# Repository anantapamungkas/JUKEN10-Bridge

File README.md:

# JUKEN10 Bridge

Repositori ini berisi berkas desain elektronik JUKEN10 Bridge yang dibuat menggunakan KiCad. Desain skematik dibagi ke beberapa bagian agar rangkaian lebih mudah ditinjau dan dikembangkan.

## Isi repositori

- `JUKEN10 Bridge.kicad_pro` — berkas proyek KiCad.
- `JUKEN10 Bridge.kicad_sch` — skematik utama proyek.
- `JUKEN10 Bridge.kicad_pcb` — berkas tata letak PCB.
- `Section A - Power.kicad_sch` — bagian rangkaian catu daya.
- `Section B - MCU_sch.kicad_sch` — bagian rangkaian mikrokontroler.
- `Section C - Throtle.kicad_sch` — bagian rangkaian throttle.
- `Section D - Input.kicad_sch` — bagian rangkaian input.
- `Section E - Analog Input.kicad_sch` — bagian rangkaian input analog.
- `project_architecture.kicad_sch` — skematik arsitektur proyek.

## Membuka proyek

1. Pasang KiCad 10 atau versi yang lebih baru.
2. Buka `JUKEN10 Bridge.kicad_pro` melalui KiCad.
3. Gunakan **Schematic Editor** untuk meninjau skematik dan **PCB Editor** untuk melihat tata letak papan.

## Catatan

Berkas kunci sementara, preferensi lokal KiCad, cache footprint, dan folder cadangan otomatis tidak disertakan dalam kontrol versi. Lihat [`.gitignore`](./.gitignore).

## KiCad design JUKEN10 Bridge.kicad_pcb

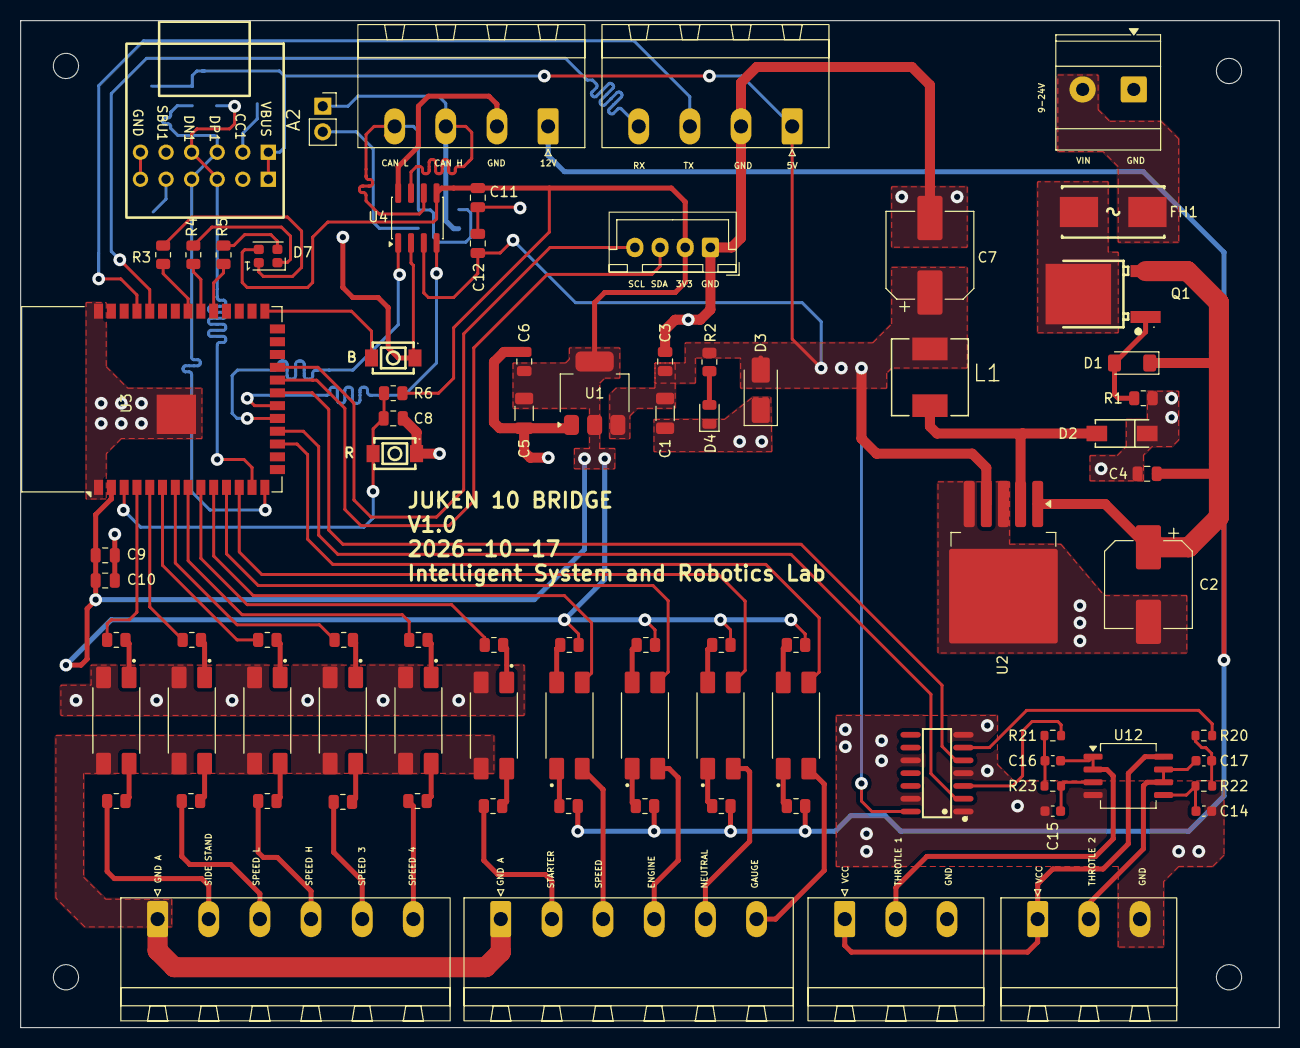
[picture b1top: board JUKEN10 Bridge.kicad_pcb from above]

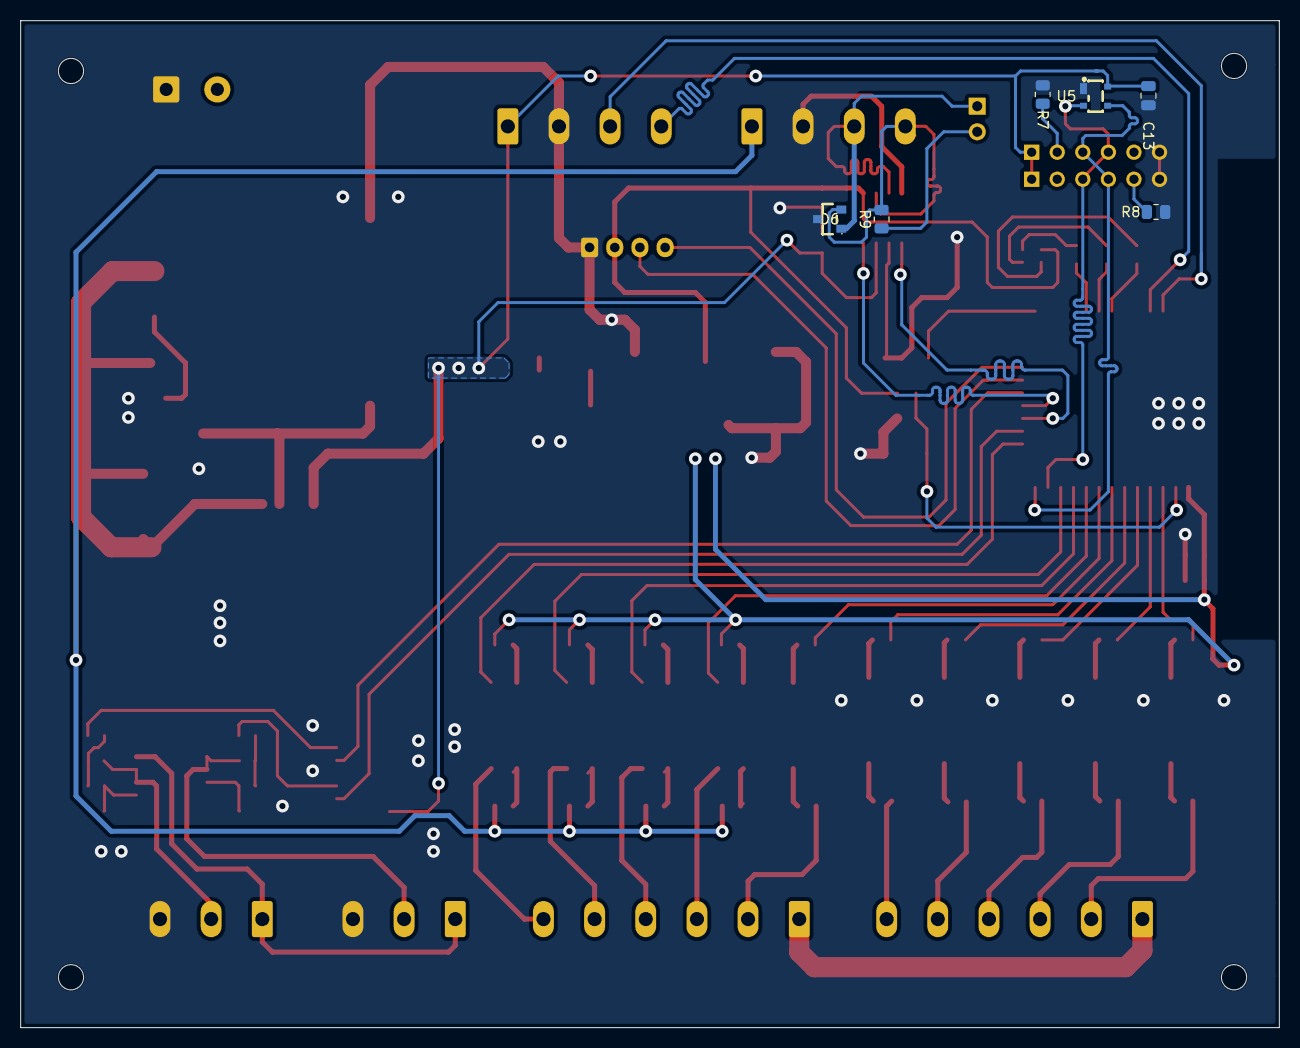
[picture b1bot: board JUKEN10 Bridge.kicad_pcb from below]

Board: 2 copper layers, 125.0 x 100.0 mm, 92 parts (6 on the bottom side), 82 nets.

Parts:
A2: Adapter Type C; USB-C_BREAKOUT_6P_TH
C1, C5: 4.7uF; C_1206_3216Metric
C2, C7: 220uF; CP_Elec_8x10.5
C3, C4, C6, C8: 1uF; C_0805_2012Metric
C9, C11, C12: 100nF; C_0805_2012Metric
C10: 10uF; C_0805_2012Metric
C13: 10uF 10V; C_0805_2012Metric
C14, C15, C16, C17: 100n; C_0603_1608Metric
D1: BZV55B12; D_MiniMELF
D2: SS34; SMA_L4.4-W2.8-LS5.4-R-RD
D3: D_TVS; D_SMA
D4: Blue; LED_0805_2012Metric
D6: PESD1CAN,215; SOT-23_L2.9-W1.3-P1.90-LS2.4-BR
D7: LED_RGBA; LED_RGB_Lumex_SML-LXT0805SIUGUBW
FH1: 01550900M; FUSE-SMD_L9.8-W5.0_01550900M
H1, H2, H3, H4: MountingHole; MountingHole_2.5mm
J1: Screw_Terminal_01x02; TerminalBlock_Phoenix_MKDS-3-2-5.08_1x02_P5.08mm_Horizontal
J2: Conn_01x04_Pin; JST_XH_B4B-XH-A_1x04_P2.50mm_Vertical
J4: Conn_01x02_Pin; PinSocket_1x02_P2.54mm_Vertical
J5: CAN BUS; PhoenixContact_MSTBA_2,5_4-G-5,08_1x04_P5.08mm_Horizontal
J6: UART; PhoenixContact_MSTBA_2,5_4-G-5,08_1x04_P5.08mm_Horizontal
J7: C03; PhoenixContact_MSTBA_2,5_6-G-5,08_1x06_P5.08mm_Horizontal
J8: THROTLE 1; PhoenixContact_MSTBA_2,5_3-G-5,08_1x03_P5.08mm_Horizontal
J9: THROTHLE 2; PhoenixContact_MSTBA_2,5_3-G-5,08_1x03_P5.08mm_Horizontal
J10: C05; PhoenixContact_MSTBA_2,5_6-G-5,08_1x06_P5.08mm_Horizontal
L1: 33uH; INDM7676X435N
Q1: IRFR5305; TO-252-3_L6.6-W6.1-P4.58-LS10.1-BR-1
R1: 100K; R_0805_2012Metric
R2: 2.2K; R_0805_2012Metric
R3, R4, R5: 1K; R_0805_2012Metric
R6: 10K; R_0805_2012Metric
R7, R8: 5.1K; R_0805_2012Metric
R9: 120R; R_0805_2012Metric
R10, R11, R12, R13, R14, R15, R16, R17, R18, R19, R24, R25, R26, R27, R28, R29, R30, R31, R32, R33: 2K2; R_0805_2012Metric
R20, R21, R22, R23: 15K; R_0603_1608Metric
SW1, SW2: TACTILE SWITCH; KEY-SMD_L4.0-W3.0-LS4.9-1
U1: AMS1117-3.3; SOT-223-3_TabPin2
U2: LM2596S-5; TO-263-5_TabPin3
U3: ESP32-S3-WROOM-1
U4: MCP2562-E-SN; SOIC-8_3.9x4.9mm_P1.27mm
U5: PESD2ETH-AXR_C5310973; SOT-143_L2.9-W1.3-P1.92-LS2.3-BL
U6, U7, U8, U9, U10, U13, U14, U15, U16, U17: PC817X2NIP1B; SOIC254P960X420-4N
U11: 74HCT125D,653; SOIC-14_L8.7-W3.9-P1.27-LS6.0-BL
U12: LMV358; SOIC-8_5.3x6.2mm_P1.27mm

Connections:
+3.3V: C5.1, C6.1, C9.2, C10.2, C11.1, D7.4 (A), J2.2, R6.1, R25.1, R26.1, R27.1, R28.1, U1.2 (VO), U3.2 (3V3), U4.5 (Vio)
+5V: A2.1 (VCC), A2.12 (VCC), C1.1, C3.1, C7.1, C12.1, C13.1, D3.2 (A2), J6.1, L1.2, R2.1, U1.3 (VI), U2.4 (FB), U4.3 (VDD), U5.4, U11.14 (VCC)
+12V: C2.1, C4.1, D1.1 (K), J5.1, Q1.3 (S), R30.2, R31.2, R32.2, R33.2, U2.1 (VIN)
/Project Architecture/Section B - CORE/Analog_1: C16.2, J8.2, U12.1, U12.2 (-)
/Project Architecture/Section B - CORE/Analog_2: C17.2, J9.2, U12.6 (-), U12.7
/Project Architecture/Section B - CORE/CAN_RX: U3.20 (IO12), U4.4 (RXD)
/Project Architecture/Section B - CORE/CAN_TX: U3.19 (IO11), U4.1 (TXD)
/Project Architecture/Section B - CORE/DAC_1: R21.1, U11.3 (1Y)
/Project Architecture/Section B - CORE/DAC_2: R20.1, U11.6 (2Y)
/Project Architecture/Section B - CORE/ENGINE: U3.11 (IO18), U15.3
/Project Architecture/Section B - CORE/GAUGE: U3.17 (IO9), U17.3
/Project Architecture/Section B - CORE/IN1: J10.3, U14.2
/Project Architecture/Section B - CORE/IN2: J10.4, U15.2
/Project Architecture/Section B - CORE/IN3: J10.5, U16.2
/Project Architecture/Section B - CORE/IN4: J10.6, U17.2
/Project Architecture/Section B - CORE/LED_B: R5.1, U3.31 (IO38)
/Project Architecture/Section B - CORE/LED_G: R4.1, U3.32 (IO39)
/Project Architecture/Section B - CORE/LED_R: R3.1, U3.33 (IO40)
/Project Architecture/Section B - CORE/NEUTRAL: U3.12 (IO8), U16.3
/Project Architecture/Section B - CORE/OUT1: J10.2, R29.1
/Project Architecture/Section B - CORE/RX: J6.4, U3.36 (RXD0)
/Project Architecture/Section B - CORE/S1: J7.2, R15.1
/Project Architecture/Section B - CORE/S2: J7.3, R16.1
/Project Architecture/Section B - CORE/S3: J7.4, R17.1
/Project Architecture/Section B - CORE/S4: J7.5, R18.1
/Project Architecture/Section B - CORE/S5: J7.6, R19.1
/Project Architecture/Section B - CORE/SIDE_STAND: R10.2, U3.4 (IO4)
/Project Architecture/Section B - CORE/SPEED: U3.10 (IO17), U14.3
/Project Architecture/Section B - CORE/SPEED_3: R13.2, U3.7 (IO7)
/Project Architecture/Section B - CORE/SPEED_4: R14.2, U3.8 (IO15)
/Project Architecture/Section B - CORE/SPEED_H: R12.2, U3.6 (IO6)
/Project Architecture/Section B - CORE/SPEED_L: R11.2, U3.5 (IO5)
/Project Architecture/Section B - CORE/STARTER: R24.2, U3.9 (IO16)
/Project Architecture/Section B - CORE/THROTLE_1: U3.18 (IO10), U11.2 (1A)
/Project Architecture/Section B - CORE/THROTLE_2: U3.21 (IO13), U11.5 (2A)
/Project Architecture/Section B - CORE/TX: J6.3, U3.37 (TXD0)
/Project Architecture/Section B - CORE/USB_D+: A2.3 (DP1), A2.9 (DP2), U3.14 (USB_D+), U5.3
/Project Architecture/Section B - CORE/USB_D-: A2.4 (DN1), A2.10 (DN2), U3.13 (USB_D-), U5.2
GND: A2.6 (GND), A2.7 (GND), C1.2, C2.2, C3.2, C4.2, C5.2, C6.2, C7.2, C8.1, C9.1, C10.1, C11.2, C12.2, C13.2, C14.2, C15.2, D2.2 (A), D3.1 (A1), D4.1 (K), D6.3, J1.1, J2.1, J5.2, J6.2, J8.3, J9.3, R1.1, R7.2, R8.2, SW1.1, SW2.1, U1.1 (GND), U2.3 (GND), U2.5 (~ON/OFF), U3.1 (GND), U3.40 (GND), U3.41 (GND), U4.2 (VSS), U4.8 (STBY), U5.1, U6.2, U7.2, U8.2, U9.2, U10.2, U11.1 (~1OE), U11.4 (~2OE), U11.7 (GND), U11.10 (~3OE), U11.13 (~4OE), U12.4 (V-), U13.2
GNDA: J7.1, J10.1, U6.3, U7.3, U8.3, U9.3, U10.3, U13.3
unnamed: A2.2 (CC1), R7.1
unnamed: A2.8 (CC2), R8.1
unnamed: C16.1, R21.2, R23.1
unnamed: C17.1, R20.2, R22.1
unnamed: D1.2 (A), Q1.1 (G), R1.2
unnamed: D2.1 (K), L1.1, U2.2 (OUT)
unnamed: D4.2 (A), R2.2
unnamed: D7.3 (BK), R5.2
unnamed: D7.2 (GK), R4.2
unnamed: D7.1 (RK), R3.2
unnamed: FH1.1, J1.2
unnamed: D6.1, J4.1, J5.3, U4.7 (CANH)
unnamed: J4.2, R9.1
unnamed: D6.2, J5.4, R9.2, U4.6 (CANL)
unnamed: FH1.2, Q1.2 (D)
unnamed: R10.1, U6.1
unnamed: R11.1, U7.1
unnamed: R12.1, U8.1
unnamed: R13.1, U9.1
unnamed: R14.1, U10.1
unnamed: R15.2, U6.4
unnamed: R16.2, U7.4
unnamed: R17.2, U8.4
unnamed: R18.2, U9.4
unnamed: R19.2, U10.4
unnamed: R24.1, U13.1
unnamed: R25.2, U14.4
unnamed: R26.2, U15.4
unnamed: R27.2, U16.4
unnamed: R28.2, U17.4
unnamed: R29.2, U13.4
unnamed: R30.1, U14.1
unnamed: R31.1, U15.1
unnamed: R32.1, U16.1
unnamed: R33.1, U17.1
unnamed: C8.2, R6.2, SW1.2, U3.3 (EN)
unnamed: SW2.2, U3.27 (IO0)
unnamed: C15.1, R23.2, U12.3 (+)
unnamed: C14.1, R22.2, U12.5 (+)
SCL: J2.4, U3.23 (IO21)
SDA: J2.3, U3.22 (IO14)
VCC: J8.1, J9.1, U12.8 (V+)
